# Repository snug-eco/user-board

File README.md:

# Snug User Board

KiCad schematic and PCB layout for the snug user board.
This board is intended for private single-person use.
Kernel flashing is supported through the AVR ISP IDC socket.
Terminal UART work over USB serial through a USB-B socket,
which also provides power for the board.
During operation, the board switches its SPI bus to the SD-Card slot.
Port C of the ATmega1284 is broken out to a 10-Pin socket
and can thus be appropriated by the user for additional functionality.

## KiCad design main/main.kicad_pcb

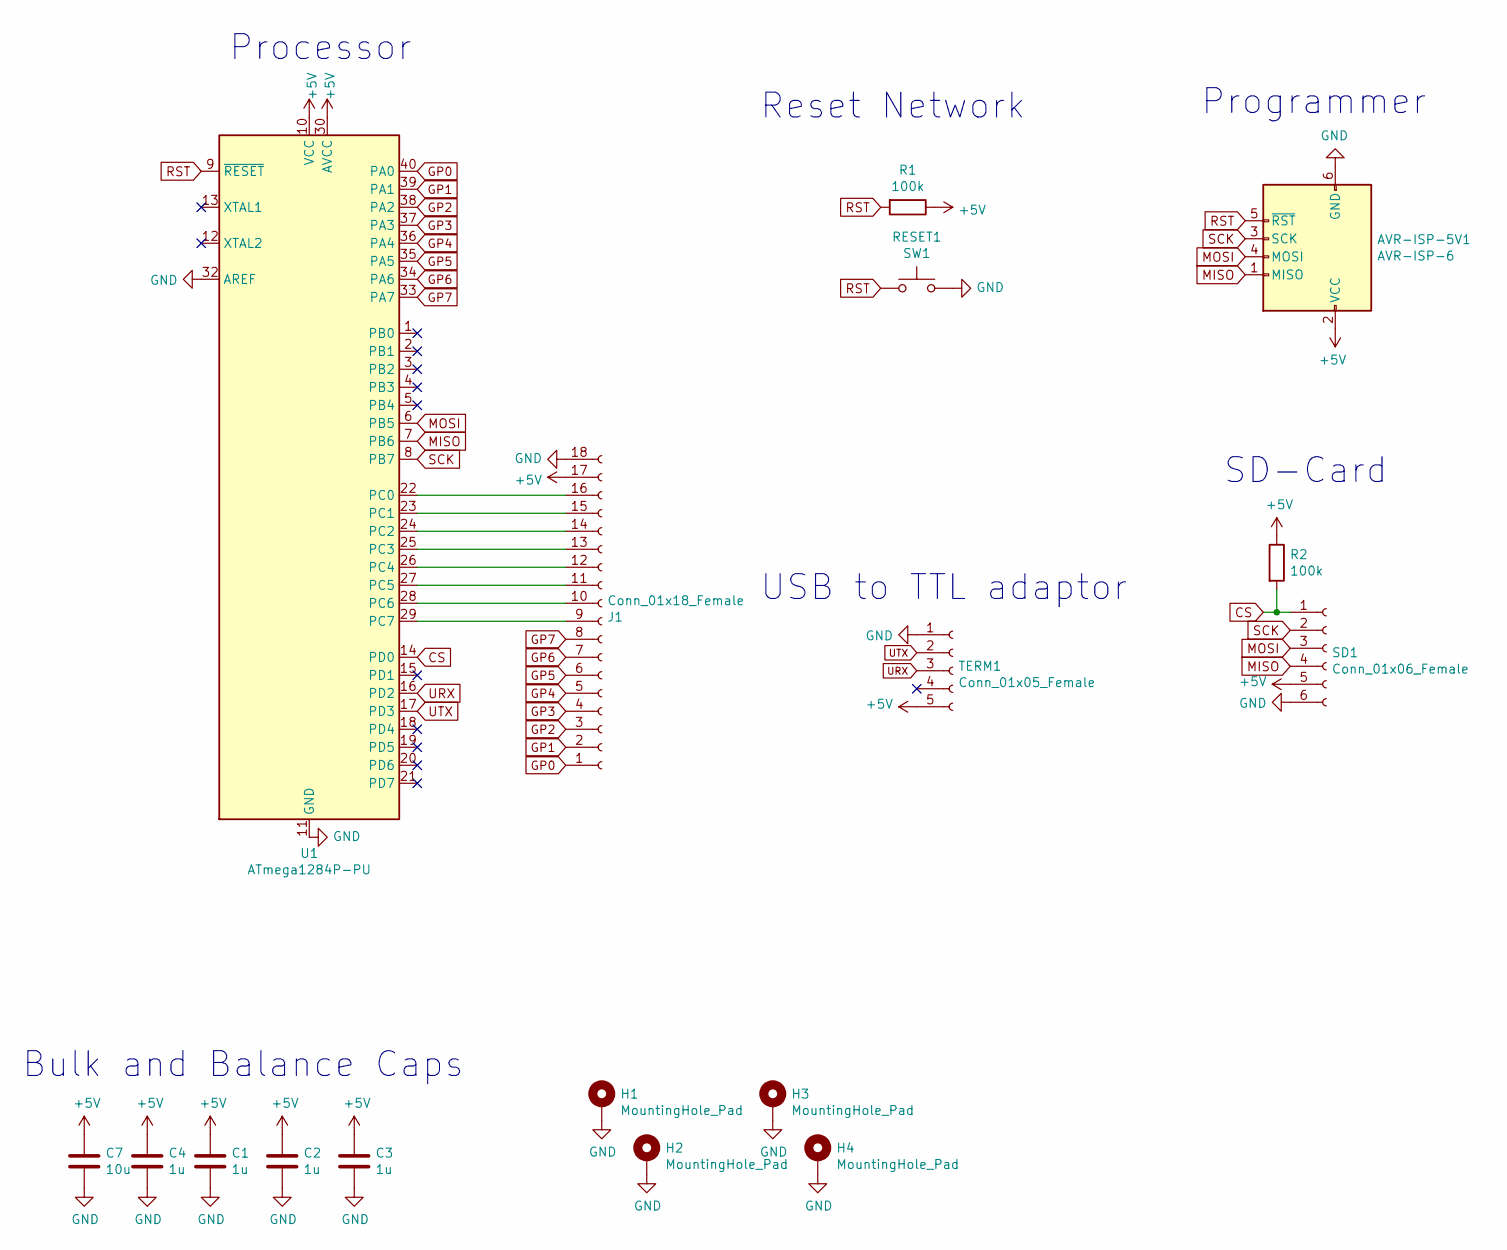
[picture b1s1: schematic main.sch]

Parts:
AVR-ISP-5V1: AVR-ISP-6; IDC-Header_2x03_P2.54mm_Vertical
C1, C2, C3, C4: 1u; C_1206_3216Metric
C7: 10u; C_1206_3216Metric
H1, H2, H3, H4: MountingHole_Pad; MountingHole_3.2mm_M3_DIN965_Pad
J1: Conn_01x18_Female; PinHeader_1x18_P2.54mm_Vertical
R1, R2: 100k; R_1210_3225Metric
RESET1: SW1; SW_PUSH_6mm_H4.3mm
SD1: Conn_01x06_Female; PinHeader_1x06_P2.54mm_Vertical
TERM1: Conn_01x05_Female; PinSocket_1x05_P2.54mm_Vertical
U1: ATmega1284P-PU; DIP-40_W15.24mm_Socket

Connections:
+5V: AVR-ISP-5V1.2 (VCC), C1.1, C2.1, C3.1, C4.1, C7.2, J1.17, R1.1, R2.1, SD1.5, TERM1.5, U1.10 (VCC), U1.30 (AVCC)
CS: R2.2, SD1.1, U1.14 (PD0)
GND: AVR-ISP-5V1.6 (GND), C1.2, C2.2, C3.2, C4.2, C7.1, H1.1, H2.1, H3.1, H4.1, J1.18, RESET1.2, SD1.6, TERM1.1, U1.11 (GND), U1.31 (GND), U1.32 (AREF)
GP0: J1.1, U1.40 (PA0)
GP1: J1.2, U1.39 (PA1)
GP2: J1.3, U1.38 (PA2)
GP3: J1.4, U1.37 (PA3)
GP4: J1.5, U1.36 (PA4)
GP5: J1.6, U1.35 (PA5)
GP6: J1.7, U1.34 (PA6)
GP7: J1.8, U1.33 (PA7)
MISO: AVR-ISP-5V1.1 (MISO), SD1.4, U1.7 (PB6)
MOSI: AVR-ISP-5V1.4 (MOSI), SD1.3, U1.6 (PB5)
unnamed: J1.9, U1.29 (PC7)
unnamed: J1.10, U1.28 (PC6)
unnamed: J1.11, U1.27 (PC5)
unnamed: J1.12, U1.26 (PC4)
unnamed: J1.13, U1.25 (PC3)
unnamed: J1.14, U1.24 (PC2)
unnamed: J1.15, U1.23 (PC1)
unnamed: J1.16, U1.22 (PC0)
RST: AVR-ISP-5V1.5 (~RST), R1.2, RESET1.1, U1.9 (~RESET)
SCK: AVR-ISP-5V1.3 (SCK), SD1.2, U1.8 (PB7)
URX: TERM1.3, U1.16 (PD2)
UTX: TERM1.2, U1.17 (PD3)

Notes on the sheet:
Processor
Bulk and Balance Caps
Reset Network
Programmer
SD-Card
USB to TTL adaptor

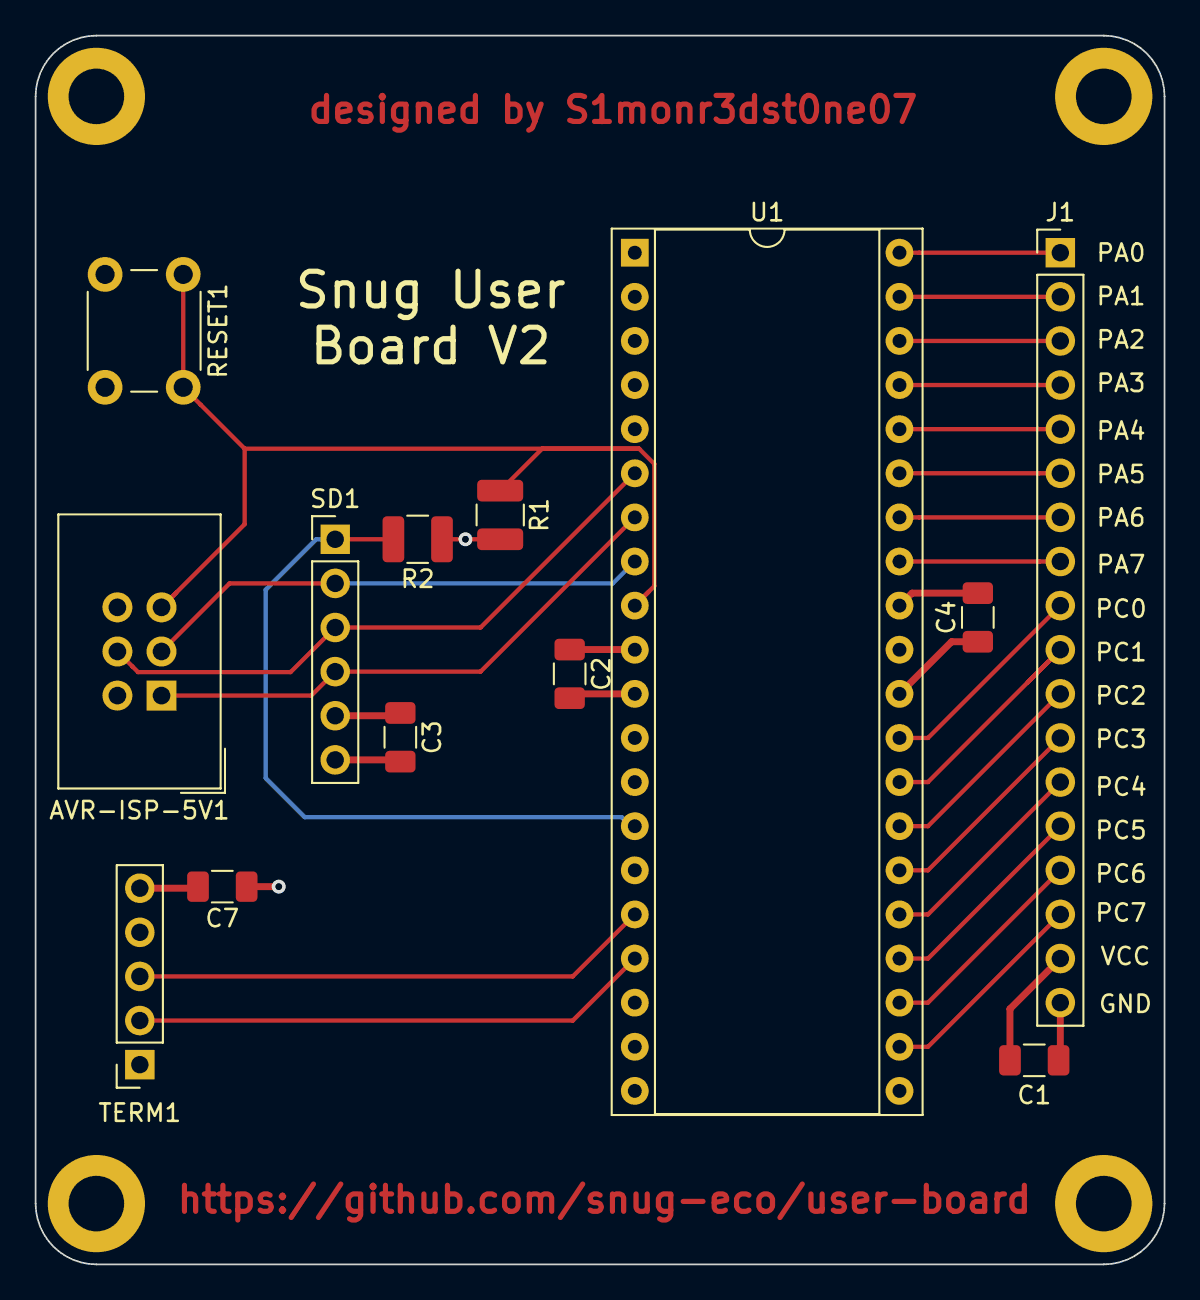
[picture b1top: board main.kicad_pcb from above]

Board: 4 copper layers, 65.0 x 70.8 mm, 17 parts (0 on the bottom side), 25 nets.

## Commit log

2025-11-26 finished general board schematic
2025-11-26 fixed footprints
2025-11-26 laid out pcb
2025-11-26 added component libraries
2025-11-26 added gitignore
2025-11-27 added mounting holes
2025-11-27 fixed 3.3v regulator cap
2025-11-27 fixed bulking caps
2025-11-27 fixed stuff
2025-11-27 added README.md
2025-11-27 fixed sd card footprint
2025-11-27 fixed layout
2025-11-27 added gerbers directory to gitignore
2025-11-28 fixed component fp text
2025-11-28 annotated schematic
2025-11-28 fixed library paths
2025-12-02 fixed silkscreen stuff
2025-12-02 fixed sd card pad distance
2025-12-23 designed V2
2025-12-26 removed unnecessary usb-b port
